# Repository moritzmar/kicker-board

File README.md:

# Kicker-Board

This is an university project by the students
- P. Hanneken
- J. Huptas
- K-A. Lehmann
- J. Linssen
- M. Martinius
- J. Niehr
- F. Schneider

It demonstrates the use of the RFM24W RF module
for simple communications between a master node and a slave node.

## Hardware

For schematics and board files refer to the schematics folder.

## Software

The software is written in arduino-c and should work on standard Arduinos.
Please note the custom Board config for the arduino-IDE.
It makes heavy use of the RadioHead arduino library, refer to their
documentation regarding RF communications.

## License

This program is free software: you can redistribute it and/or modify
it under the terms of the GNU General Public License as published by
the Free Software Foundation, either version 3 of the License, or
(at your option) any later version.

This program is distributed in the hope that it will be useful,
but WITHOUT ANY WARRANTY; without even the implied warranty of
MERCHANTABILITY or FITNESS FOR A PARTICULAR PURPOSE.  See the
GNU General Public License for more details.

You should have received a copy of the GNU General Public License
along with this program.  If not, see <http://www.gnu.org/licenses/>.

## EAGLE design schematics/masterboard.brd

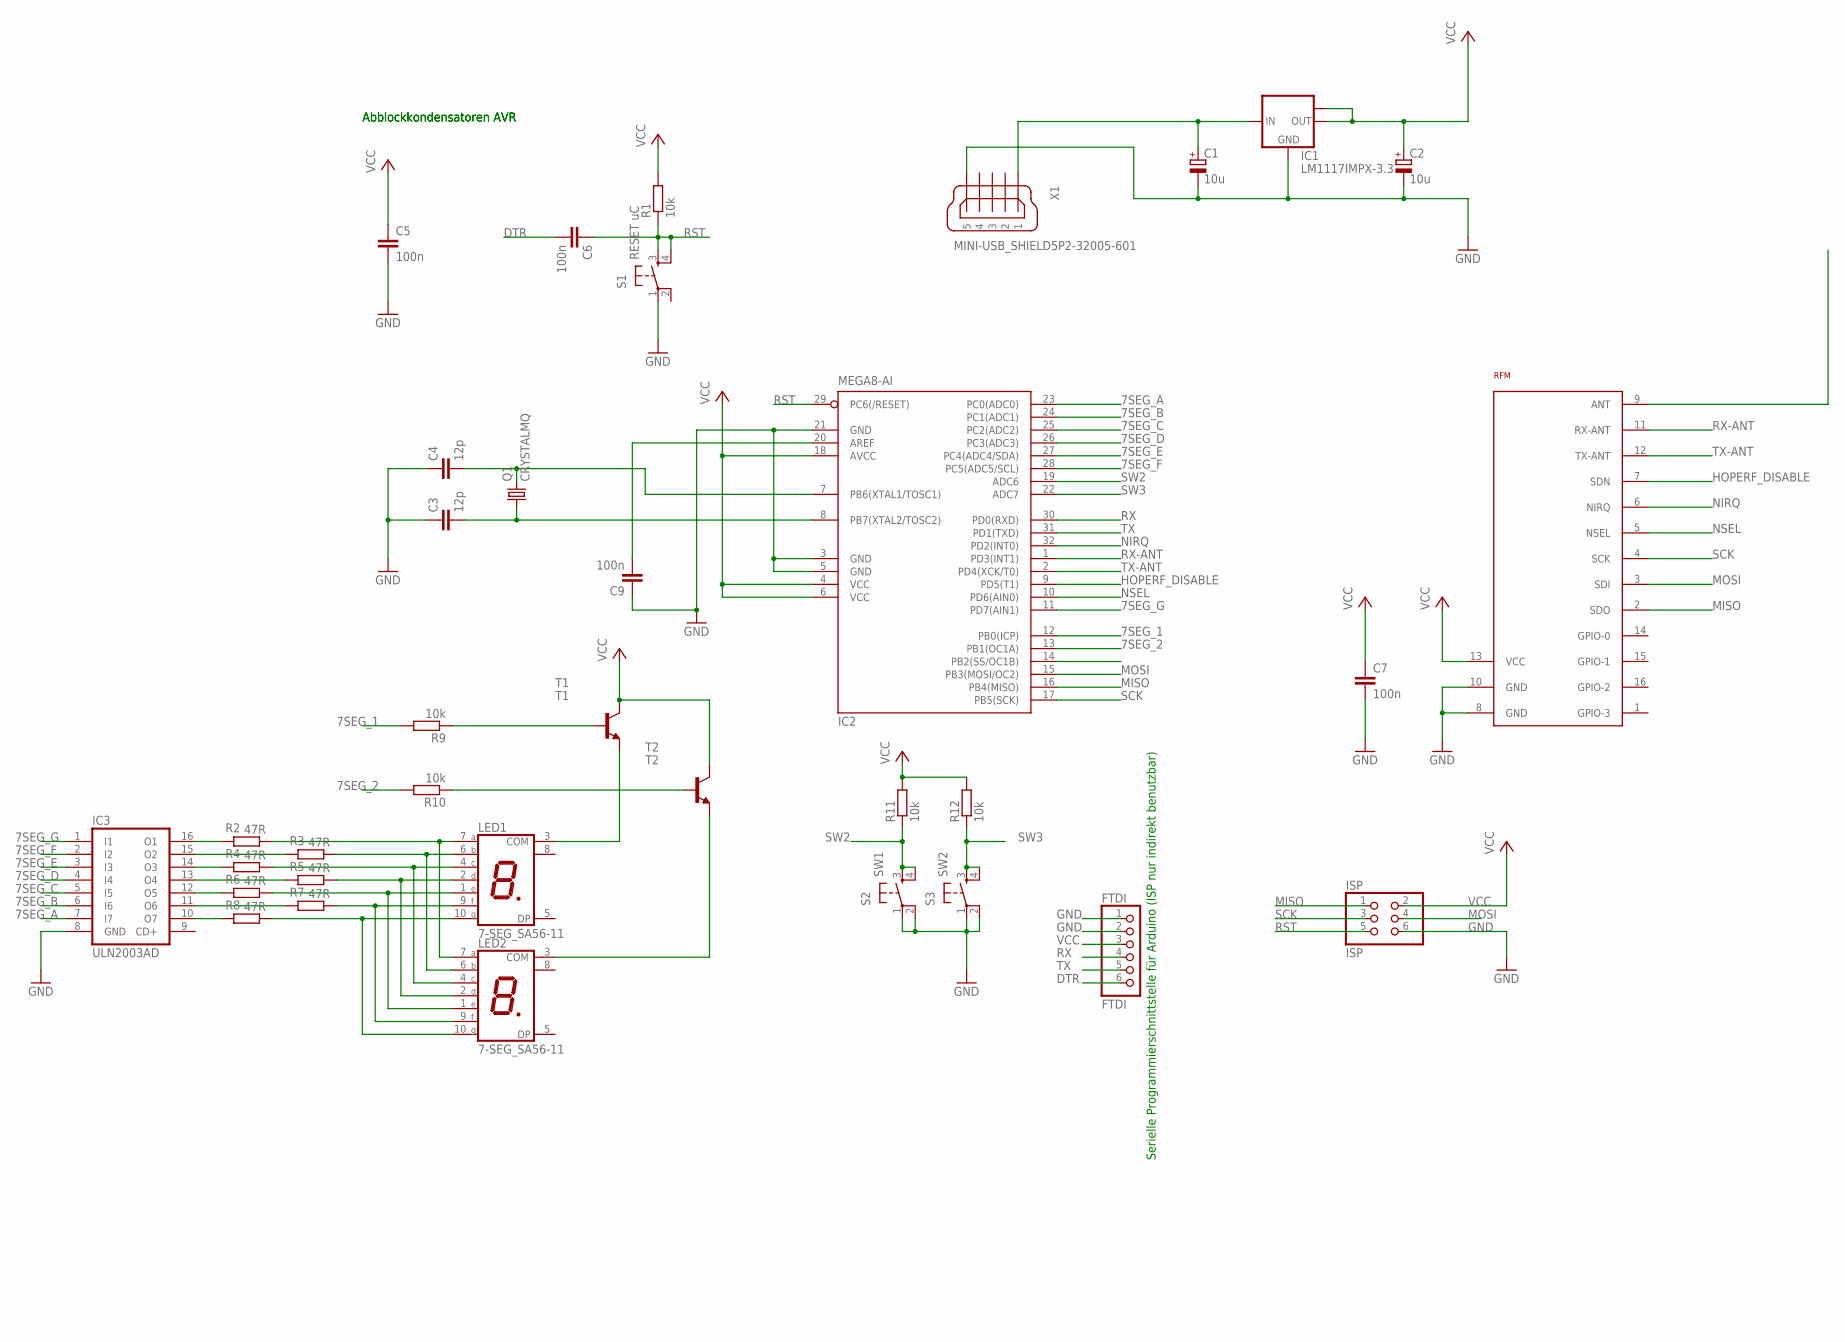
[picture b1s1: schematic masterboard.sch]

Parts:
C1, C2: 10u; CT6032
C3, C4: 12p; C0603
C5, C6, C7, C9: 100n; C0603
FTDI: FTDI; 1X06/90
IC1: LM1117IMPX-3.3; SOT223
IC2: MEGA8-AI; TQFP32-08
IC3: ULN2003AD; SO16
ISP: ISP; 2X03
LED1, LED2: 7-SEG_SA56-11; SA56-11
Q1: CRYSTALMQ; MQ
R1, R9, R10, R11, R12: 10k; R0805
R2, R3, R4, R5, R6, R7, R8: 47R; R0805
RFM: HOPERF-DB
S1: RESET uC; RAFI
S2: SW1; RAFI
S3: SW2; RAFI
T1: T1; SOT89-BCE
T2: T2; SOT89-BCE
X1: MINI-USB_SHIELD5P2-32005-601; 32005-601

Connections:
7SEG_1: IC2.12 (PB0(ICP)), R9.2
7SEG_2: IC2.13 (PB1(OC1A)), R10.2
7SEG_A: IC2.23 (PC0(ADC0)), IC3.7 (I7)
7SEG_B: IC2.24 (PC1(ADC1)), IC3.6 (I6)
7SEG_C: IC2.25 (PC2(ADC2)), IC3.5 (I5)
7SEG_D: IC2.26 (PC3(ADC3)), IC3.4 (I4)
7SEG_E: IC2.27 (PC4(ADC4/SDA)), IC3.3 (I3)
7SEG_F: IC2.28 (PC5(ADC5/SCL)), IC3.2 (I2)
7SEG_G: IC2.11 (PD7(AIN1)), IC3.1 (I1)
DTR: C6.2, FTDI.6
GND: C1.-, C2.-, C3.1, C4.1, C5.2, C7.2, C9.1, FTDI.1, FTDI.2, IC1.1 (GND), IC2.3 (GND), IC2.5 (GND), IC2.21 (GND), IC3.8 (GND), ISP.6, RFM.8 (GND), RFM.10 (GND), S1.1, S2.1, S2.2 (P1), S3.1, S3.2 (P1), X1.5
HOPERF_DISABLE: IC2.9 (PD5(T1)), RFM.7 (SDN)
MISO: IC2.16 (PB4(MISO)), ISP.1, RFM.2 (SDO)
MOSI: IC2.15 (PB3(MOSI/OC2)), ISP.4, RFM.3 (SDI)
unnamed: C3.2, IC2.8 (PB7(XTAL2/TOSC2)), Q1.P1 (1)
unnamed: C4.2, IC2.7 (PB6(XTAL1/TOSC1)), Q1.P3 (2)
unnamed: C1.+, IC1.3 (IN), X1.1
unnamed: C9.2, IC2.20 (AREF)
unnamed: IC3.16 (O1), R2.2
unnamed: LED1.7 (A), LED2.7 (A), R2.1
unnamed: IC3.15 (O2), R3.2
unnamed: LED1.6 (B), LED2.6 (B), R3.1
unnamed: IC3.14 (O3), R4.2
unnamed: LED1.4 (C), LED2.4 (C), R4.1
unnamed: IC3.13 (O4), R5.2
unnamed: LED1.2 (D), LED2.2 (D), R5.1
unnamed: IC3.12 (O5), R6.2
unnamed: LED1.1 (E), LED2.1 (E), R6.1
unnamed: IC3.11 (O6), R7.2
unnamed: LED1.9 (F), LED2.9 (F), R7.1
unnamed: IC3.10 (O7), R8.2
unnamed: LED1.10 (G), LED2.10 (G), R8.1
unnamed: LED1.3 (COM), T1.E
unnamed: LED2.3 (COM), T2.E
unnamed: R10.1, T2.B
unnamed: R9.1, T1.B
NIRQ: IC2.32 (PD2(INT0)), RFM.6 (NIRQ)
NSEL: IC2.10 (PD6(AIN0)), RFM.5 (NSEL)
RST: C6.1, IC2.29 (PC6(/RESET)), ISP.5, R1.1, S1.3 (S), S1.4 (S1)
RX: FTDI.4, IC2.30 (PD0(RXD))
RX-ANT: IC2.1 (PD3(INT1)), RFM.11 (RX-ANT)
SCK: IC2.17 (PB5(SCK)), ISP.3, RFM.4 (SCK)
SW2: IC2.19 (ADC6), R11.1, S2.3 (S), S2.4 (S1)
SW3: IC2.22 (ADC7), R12.1, S3.3 (S), S3.4 (S1)
TX: FTDI.5, IC2.31 (PD1(TXD))
TX-ANT: IC2.2 (PD4(XCK/T0)), RFM.12 (TX-ANT)
VCC: C2.+, C5.1, C7.1, FTDI.3, IC1.2 (OUT), IC1.TAB (OUT1), IC2.4 (VCC), IC2.6 (VCC), IC2.18 (AVCC), ISP.2, R1.2, R11.2, R12.2, RFM.13 (VCC), T1.C, T2.C

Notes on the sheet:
Abblockkondensatoren AVR
Serielle Programmierschnittstelle für Arduino (ISP nur indirekt benutzbar)

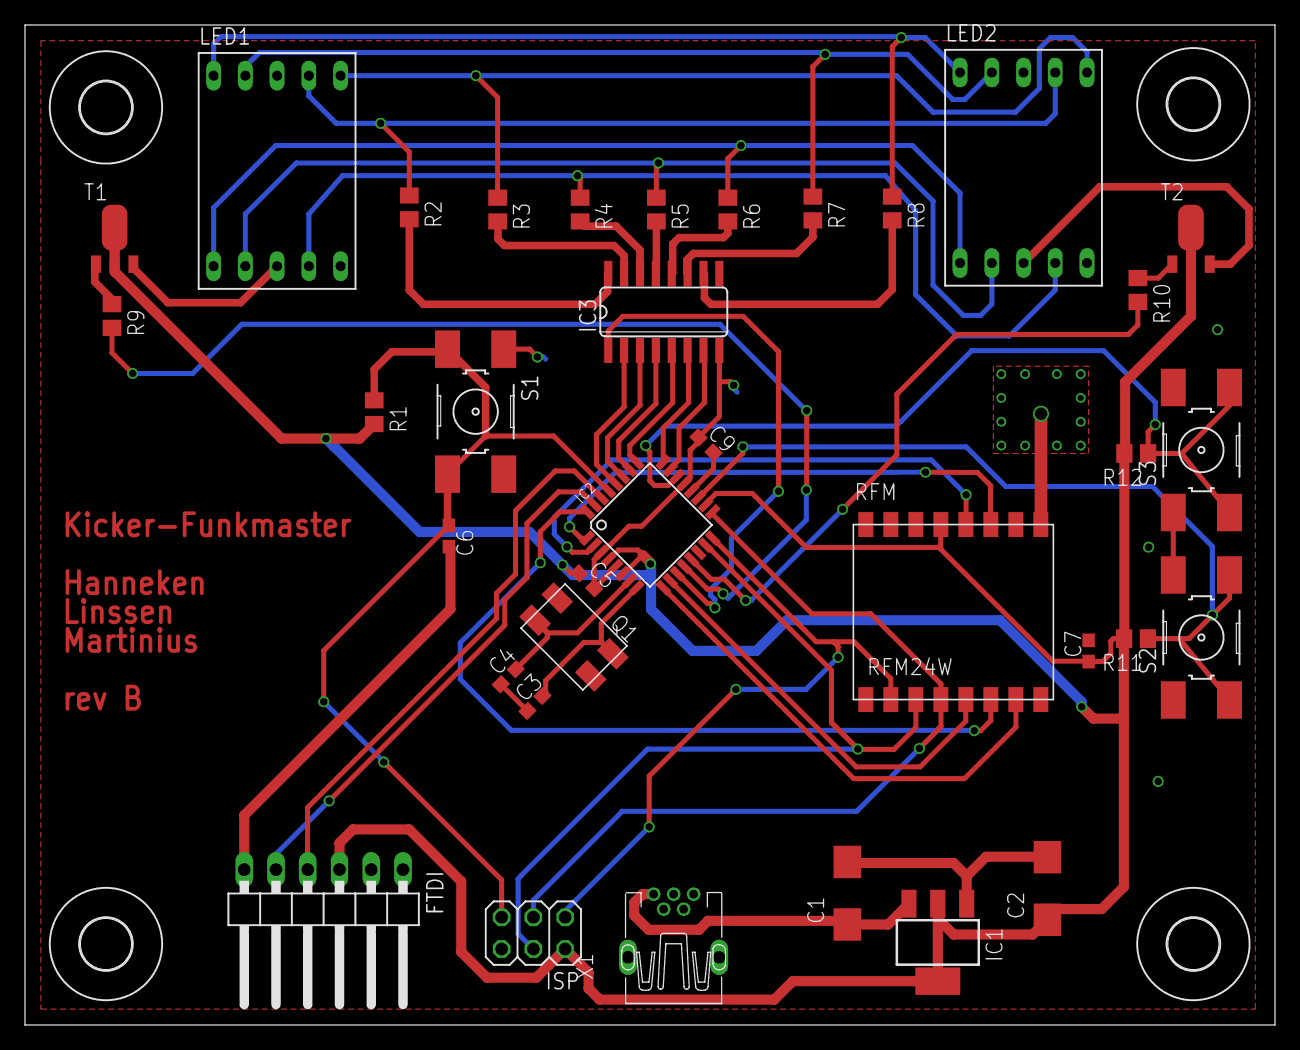
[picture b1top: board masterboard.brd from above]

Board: 2 copper layers, 100.0 x 80.0 mm, 39 parts (0 on the bottom side), 47 nets.

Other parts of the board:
U$2, U$3, U$4, U$5: 4,1

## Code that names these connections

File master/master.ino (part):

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 * Sets up the 7-segment display module. Note that the pins for the segments are scattered to PORTC and PORTD
 */
void segments_setup(void) {
  	DDRC |= ( (1 << PC0) | (1 << PC1) | (1 << PC2) | (1 << PC3) | (1 << PC4) | (1 << PC5)); // Output pins for 7 segment G-B
	DDRD |= (1 << PD7); // Output pin for 7 segment A

	DDRB |= (1 << PB0) | (1 << PB1); // 7 segment drive transistor
}

/*
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void segments_worker(uint8_t score_a, uint8_t score_b) {  // Segments multiplexing
	static uint8_t element = 0;
	if(element == 0) {
		PORTB &= ~(1 << PB1); // disable 2nd display element
		element = 1; // set flag for next element
		PORTC &= ~((1 << PC0) | (1 << PC1) | (1 << PC2) | (1 << PC3) | (1 << PC4) | (1 << PC5));
		PORTD &= ~(1 << PD7);
		PORTC |= segments_lut_1[score_a]; // set segment G-B from LUT
		PORTD |= segments_lut_2[score_a]; // set segment A from LUT
		PORTB |= (1 << PB0);  // enable 1st display segment
	}
	else {
		PORTB &= ~(1 << PB0); // disable 1st display element
		element = 0; // set flag for next element
		PORTC &= ~((1 << PC0) | (1 << PC1) | (1 << PC2) | (1 << PC3) | (1 << PC4) | (1 << PC5));
		PORTD &= ~(1 << PD7);
		PORTC |= segments_lut_1[score_b]; // set segment G-B from LUT
		PORTD |= segments_lut_2[score_b]; // set segment A from LUT
		PORTB |= (1 << PB1); // enable 2nd display segment
	}
}

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
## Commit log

2015-07-20 Initial release
2015-07-20 Testdatei gelöscht / erste Slave-Datei hinzugefügt
2015-07-20 Ich habe eine Textdatei hinzugefügt
2015-07-20 added radiohead submodule
2015-07-20 deleted deinemudda.txt
2015-07-20 Namen geändert
2015-07-20 neue SlaveA neue Master
2015-07-20 Masterdatei geändert (crc rein) slaveA datei vervollständigt und crc rein
2015-07-20 Added EAGLE schematic and board files
2015-07-20 Added libs for schematics
2015-07-20 Bitte geben Sie eine Commit-Beschreibung für Ihre Änderungen ein. Zeilen, fixed duplicate files
2015-07-20 Edited demo package
2015-07-21 Added CRC8 calculation and some slave changes
2015-07-21 Added files for slave a and b
2015-07-22 Modularized score request and general tidying
2015-07-22 small fix regarding slave reset request
2015-07-22 improved score function
2015-07-22 Slave a und b finale Version Kommentiert
2015-07-22 Lots of commenting, added license
2015-07-22 Updated README.md to some useful information
